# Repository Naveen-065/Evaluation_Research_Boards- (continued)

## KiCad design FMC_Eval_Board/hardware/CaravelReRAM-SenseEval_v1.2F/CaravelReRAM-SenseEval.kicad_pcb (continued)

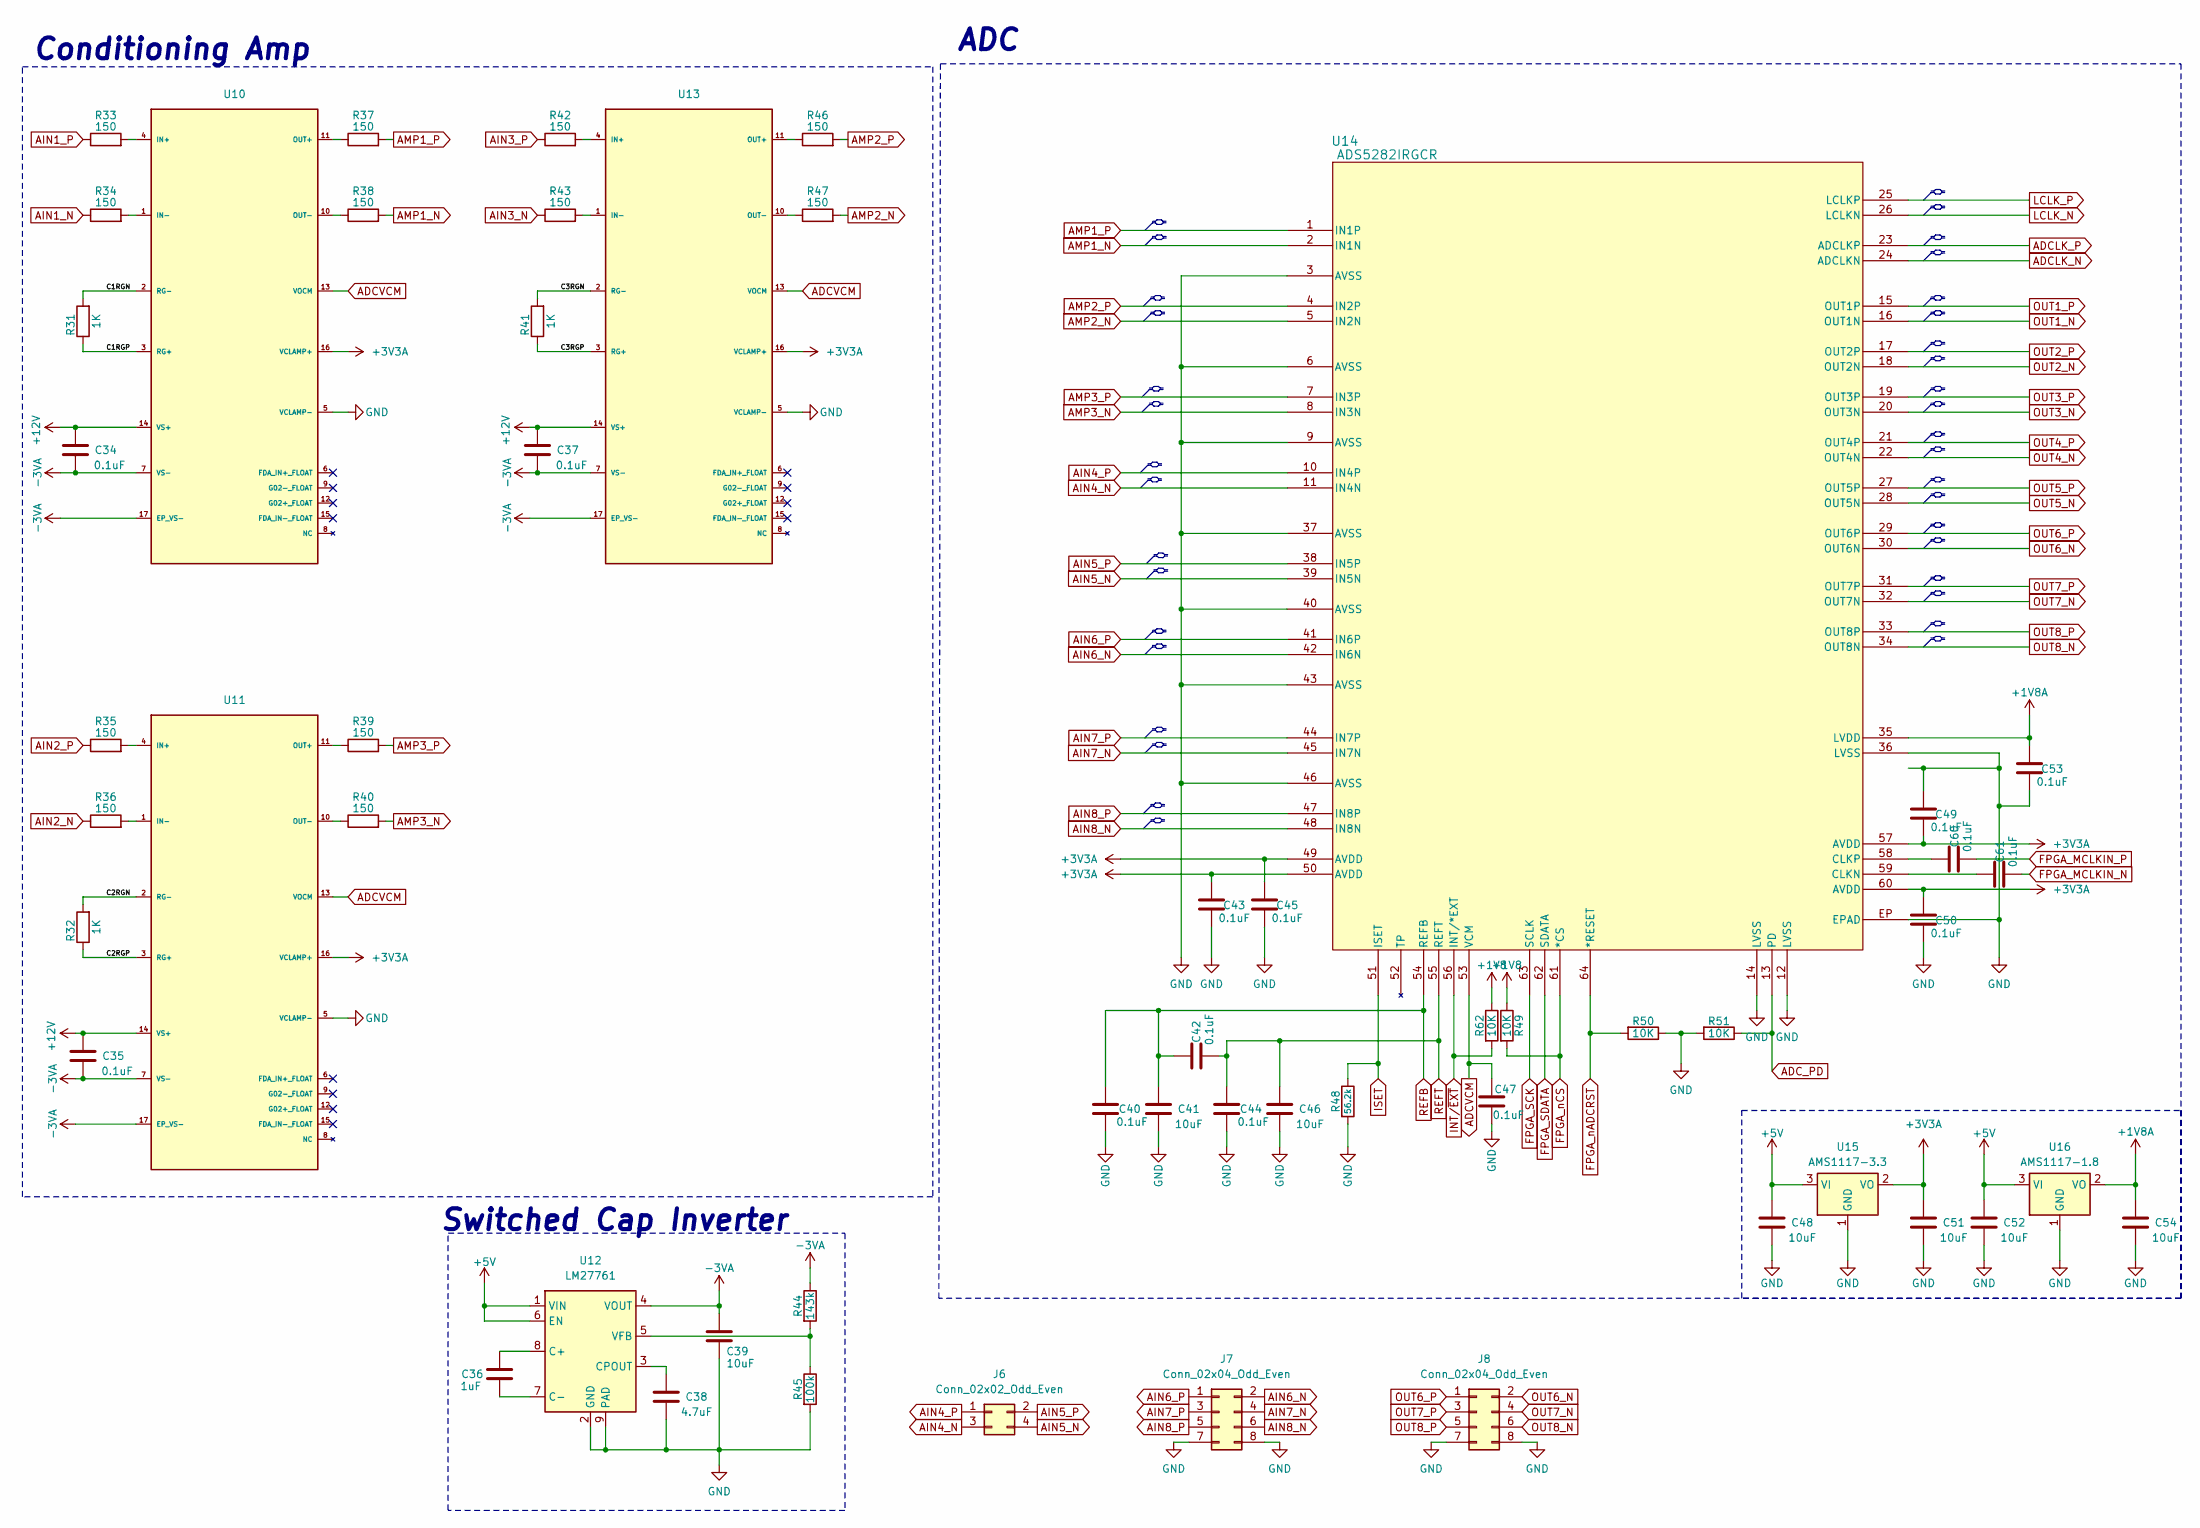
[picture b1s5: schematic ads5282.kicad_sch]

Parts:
C34, C35, C37, C40, C42, C43, C44, C45, C47, C49, C50, C53, C60, C61: 0.1uF; C_0805_2012Metric; Part # C0805C104K5RAC7411
C36: 1uF; C_0805_2012Metric; Part # 885012207103
C38: 4.7uF; C_0805_2012Metric; Part # CL21A475KBQNNNE
C39, C41, C46, C48, C51, C52, C54: 10uF; C_0805_2012Metric; Part # CL21B106KAYQNNE
J6: Conn_02x02_Odd_Even; PinHeader_2x02_P2.00mm_Vertical
J7, J8: Conn_02x04_Odd_Even; IDC-Header_2x04_P2.54mm_Vertical
R31, R32, R41: 1K; R_0805_2012Metric; Part # RC0805FR-071KL
R33, R34, R35, R36, R37, R38, R39, R40, R42, R43, R46, R47: 150; R_0805_2012Metric; Part # RNCP0805FTD150R
R44: 143k; R_0805_2012Metric; Part # RC0805FR-07143KL
R45: 100k; R_0805_2012Metric; Part # RC0805FR-07100KL
R48: 56.2k; R_0805_2012Metric; Part # RC0805FR-1356K2L
R49, R50, R51, R62: 10K; R_0805_2012Metric; Part # RC0805FR-0710KL
U10, U11, U13: INA851RGTR; VQFN16_RGT_TEX; MPN INA851RGTR
U12: LM27761; Texas_DSG0008A_WSON-8-1EP_2x2mm_P0.5mm_EP0.9x1.6mm
U14: ADS5282IRGCR; Texas_RGC0064B_VQFN-64-1EP_9x9mm_P0.5mm_EP4.25x4.25mm
U15: AMS1117-3.3; SOT-223-3_TabPin2
U16: AMS1117-1.8; SOT-223-3_TabPin2

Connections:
+1V8A: C53.2, C54.1, U14.35 (LVDD), U16.2 (VO); also elsewhere on the board
+3V3A: C43.2, C45.2, C49.1, C50.2, C51.1, U10.16 (VCLAMP+), U11.16 (VCLAMP+), U13.16 (VCLAMP+), U14.49 (AVDD), U14.50 (AVDD), U14.57 (AVDD), U14.60 (AVDD), U15.2 (VO)
+5V: C48.1, C52.1, U12.1 (VIN), U12.6 (EN), U15.3 (VI), U16.3 (VI); also elsewhere on the board
+12V: C34.2, C35.2, C37.2, U10.14 (VS+), U11.14 (VS+), U13.14 (VS+); also elsewhere on the board
-3VA: C34.1, C35.1, C37.1, C39.1, R44.1, U10.7 (VS-), U10.17 (EP_VS-), U11.7 (VS-), U11.17 (EP_VS-), U12.4 (VOUT), U13.7 (VS-), U13.17 (EP_VS-)
/ADC/C1RGN: R31.2, U10.2 (RG-)
/ADC/C1RGP: R31.1, U10.3 (RG+)
/ADC/C2RGN: R32.2, U11.2 (RG-)
/ADC/C2RGP: R32.1, U11.3 (RG+)
/ADC/C3RGN: R41.2, U13.2 (RG-)
/ADC/C3RGP: R41.1, U13.3 (RG+)
ADCLK_N: U14.24 (ADCLKN); also elsewhere on the board
ADCLK_P: U14.23 (ADCLKP); also elsewhere on the board
ADCVCM: C47.2, U10.13 (VOCM), U11.13 (VOCM), U13.13 (VOCM), U14.53 (VCM)
ADC_PD: R51.1, U14.13 (PD); also elsewhere on the board
AIN1_N: R34.1; also elsewhere on the board
AIN1_P: R33.1; also elsewhere on the board
AIN2_N: R36.1; also elsewhere on the board
AIN2_P: R35.1; also elsewhere on the board
AIN3_N: R43.1; also elsewhere on the board
AIN3_P: R42.1; also elsewhere on the board
AIN4_N: J6.3, U14.11 (IN4N)
AIN4_P: J6.1, U14.10 (IN4P)
AIN5_N: J6.4, U14.39 (IN5N)
AIN5_P: J6.2, U14.38 (IN5P)
AIN6_N: J7.2, U14.42 (IN6N)
AIN6_P: J7.1, U14.41 (IN6P)
AIN7_N: J7.4, U14.45 (IN7N)
AIN7_P: J7.3, U14.44 (IN7P)
AIN8_N: J7.6, U14.48 (IN8N)
AIN8_P: J7.5, U14.47 (IN8P)
AMP1_N: R38.2, U14.2 (IN1N)
AMP1_P: R37.2, U14.1 (IN1P)
AMP2_N: R47.2, U14.5 (IN2N)
AMP2_P: R46.2, U14.4 (IN2P)
AMP3_N: R40.2, U14.8 (IN3N)
AMP3_P: R39.2, U14.7 (IN3P)
FPGA_SCK: U14.63 (SCLK); also elsewhere on the board
FPGA_SDATA: U14.62 (SDATA); also elsewhere on the board
FPGA_nADCRST: R50.2, U14.64 (*RESET); also elsewhere on the board
FPGA_nCS: R49.2, U14.61 (*CS); also elsewhere on the board
GND: C38.2, C39.2, C40.1, C41.2, C43.1, C44.1, C45.1, C46.2, C47.1, C48.2, C49.2, C50.1, C51.2, C52.2, C53.1, C54.2, J7.7, J7.8, J8.7, J8.8, R45.2, R48.2, R50.1, R51.2, U10.5 (VCLAMP-), U11.5 (VCLAMP-), U12.2 (GND), U12.9 (PAD), U13.5 (VCLAMP-), U14.3 (AVSS), U14.6 (AVSS), U14.9 (AVSS), U14.12 (LVSS), U14.14 (LVSS), U14.36 (LVSS), U14.37 (AVSS), U14.40 (AVSS), U14.43 (LVSS), U14.46 (AVSS), U14.EP (EPAD), U15.1 (GND), U16.1 (GND); also elsewhere on the board
ISET: R48.1, U14.51 (ISET)
LCLK_N: U14.26 (LCLKN); also elsewhere on the board
LCLK_P: U14.25 (LCLKP); also elsewhere on the board
unnamed: R33.2, U10.4 (IN+)
unnamed: R34.2, U10.1 (IN-)
unnamed: R37.1, U10.11 (OUT+)
unnamed: R38.1, U10.10 (OUT-)
unnamed: R35.2, U11.4 (IN+)
unnamed: R36.2, U11.1 (IN-)
unnamed: R39.1, U11.11 (OUT+)
unnamed: R40.1, U11.10 (OUT-)
unnamed: C36.1, U12.8 (C+)
unnamed: C36.2, U12.7 (C-)
unnamed: C38.1, U12.3 (CPOUT)
unnamed: R44.2, R45.1, U12.5 (VFB)
unnamed: R42.2, U13.4 (IN+)
unnamed: R43.2, U13.1 (IN-)
unnamed: R46.1, U13.11 (OUT+)
unnamed: R47.1, U13.10 (OUT-)
OUT1_N: U14.16 (OUT1N); also elsewhere on the board
OUT1_P: U14.15 (OUT1P); also elsewhere on the board
OUT2_N: U14.18 (OUT2N); also elsewhere on the board
OUT2_P: U14.17 (OUT2P); also elsewhere on the board
OUT3_N: U14.20 (OUT3N); also elsewhere on the board
OUT3_P: U14.19 (OUT3P); also elsewhere on the board
OUT4_N: U14.22 (OUT4N); also elsewhere on the board
OUT4_P: U14.21 (OUT4P); also elsewhere on the board
OUT5_N: U14.28 (OUT5N); also elsewhere on the board
OUT5_P: U14.27 (OUT5P); also elsewhere on the board
OUT6_N: J8.2, U14.30 (OUT6P)
OUT6_P: J8.1, U14.29 (OUT6N)
OUT7_N: J8.4, U14.32 (OUT7N)
OUT7_P: J8.3, U14.31 (OUT7P)
OUT8_N: J8.6, U14.34 (OUT8N)
OUT8_P: J8.5, U14.33 (OUT8P)
REFB: C40.2, C41.1, C42.2, U14.54 (REFB)
REFT: C42.1, C44.2, C46.1, U14.55 (REFT)

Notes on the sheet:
Switched Cap Inverter
Conditioning Amp
ADC

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
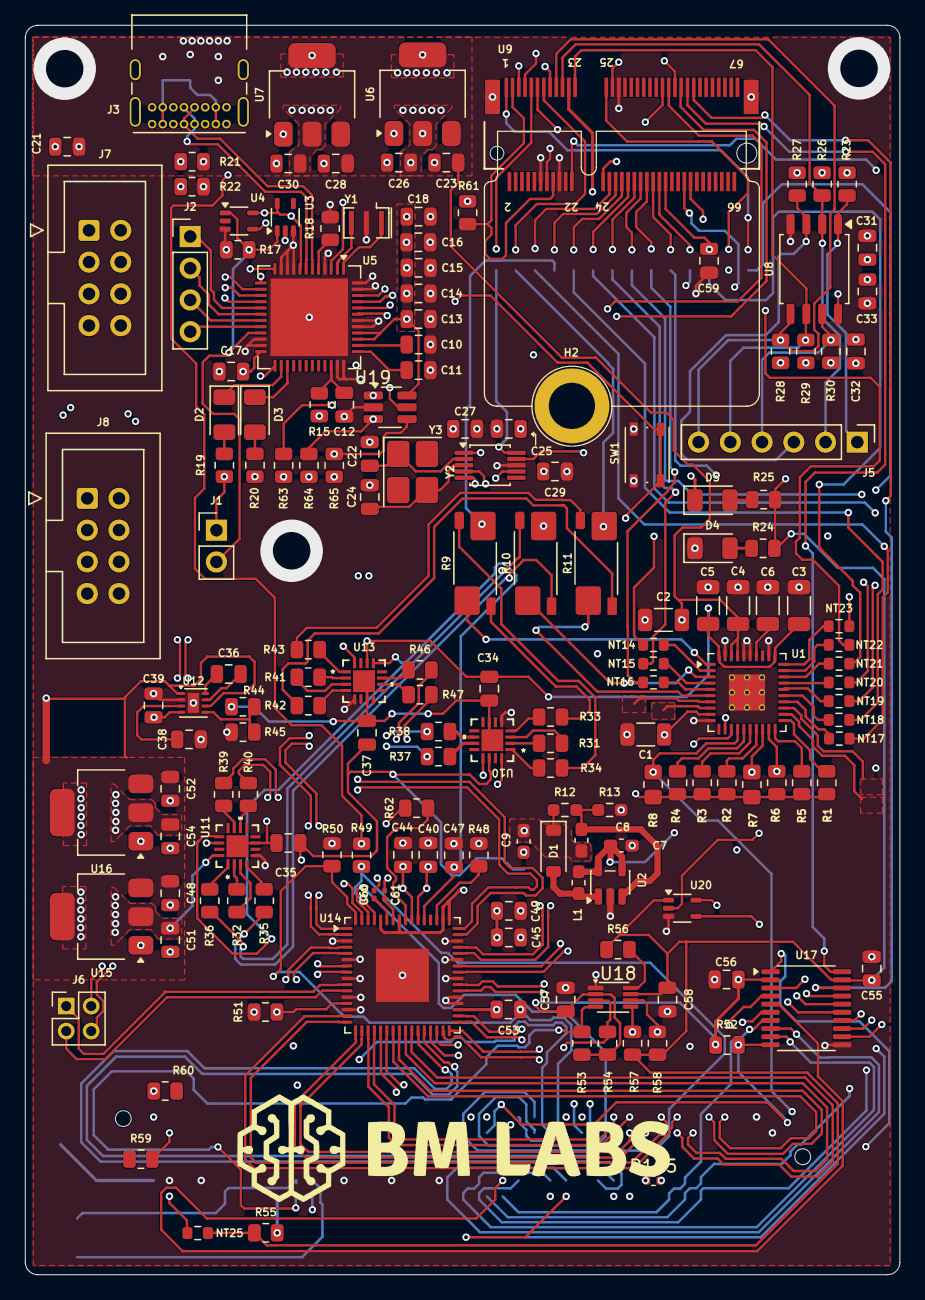
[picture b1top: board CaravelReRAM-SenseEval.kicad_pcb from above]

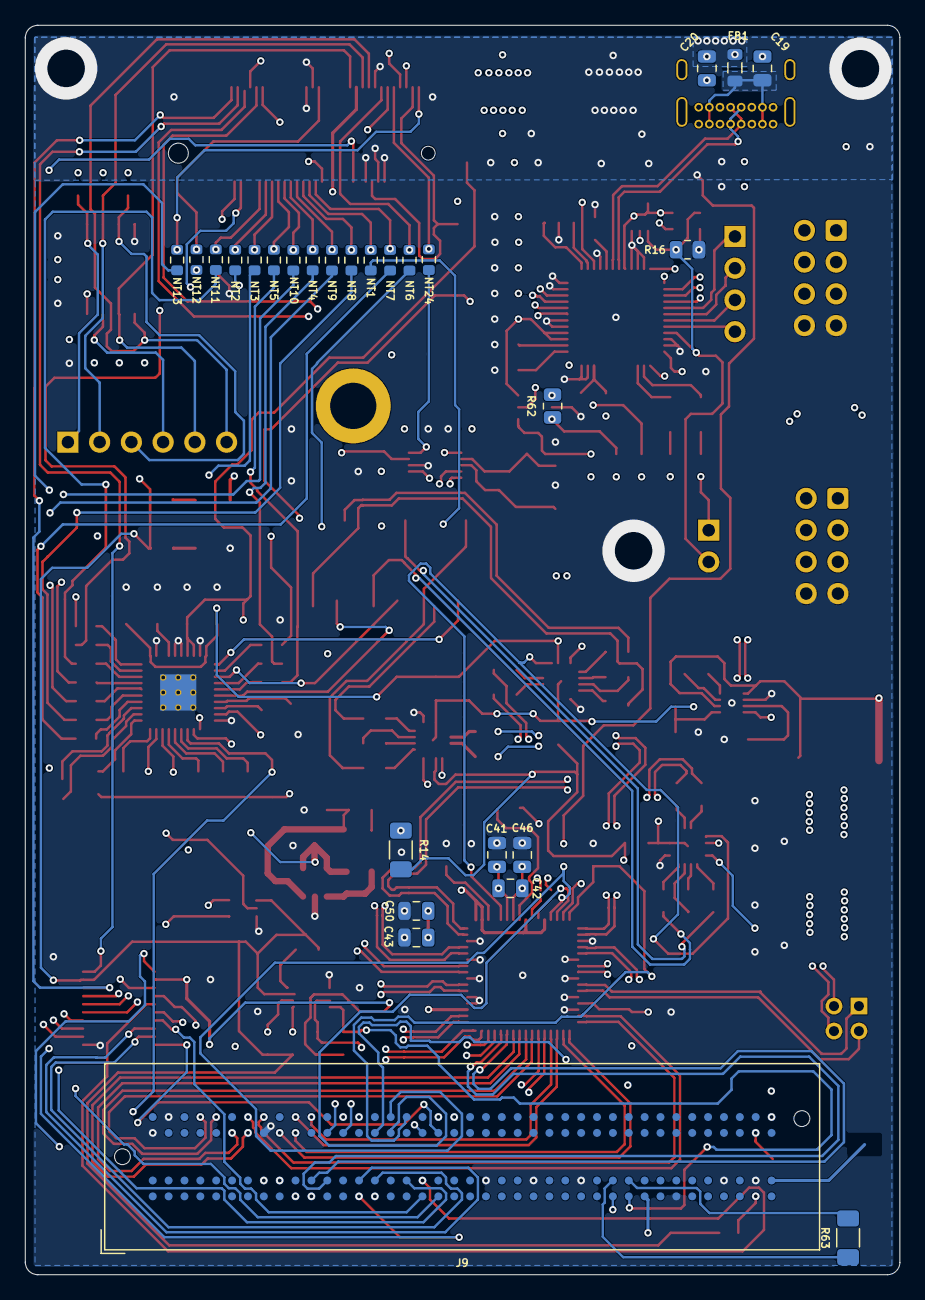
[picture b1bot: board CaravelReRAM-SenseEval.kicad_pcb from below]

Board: 6 copper layers, 70.0 x 100.0 mm, 194 parts (27 on the bottom side), 209 nets.

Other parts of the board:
R62#2: 1K; R_0805_2012Metric
R63#2: ERJ-8GEY0R00V; R_1206_3216Metric_Pad1.30x1.75mm_HandSolder

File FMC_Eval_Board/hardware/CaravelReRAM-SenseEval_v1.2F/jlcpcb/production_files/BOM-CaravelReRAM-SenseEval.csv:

Comment,Designator,Footprint,LCSC,Quantity
0,R61,R_0805_2012Metric,C17477,1
0.01uF,"C12,C19,C31",C_0805_2012Metric,C1710,3
0.1uF,"C10,C11,C13,C14,C15,C16,C17,C20,C27,C29,C32,C34,C35,C37,C40,C42,C43,C44,C45,C47,C49,C50,C53,C55,C56,C57,C58",C_0805_2012Metric,C1711,27
100k,R45,R_0805_2012Metric,C149504,1
100nF,"C1,C2,C3,C4,C5,C6",C_1206_3216Metric,C97946,6
10K,"R15,R21,R22,R23,R26,R27,R28,R29,R30,R49,R50,R51,R52,R53,R54,R55,R56,R57,R58,R59,R60,R64,R65",R_0805_2012Metric,C17414,23
10k,"R1,R2,R3,R4,R5,R6,R7,R8",R_0805_2012Metric,C17414,8
10uF,"C18,C21,C23,C25,C26,C28,C30,C39,C41,C46,C48,C51,C52,C54",C_0805_2012Metric,C15850,14
12K 1%,R18,R_0805_2012Metric,C17444,1
12MHz,Y1,Resonator_SMD_Murata_CSTxExxV-3Pin_3.0x1.1mm,C341520,1
143k,R44,R_0805_2012Metric,C2930167,1
150,"R19,R20,R33,R34,R35,R36,R37,R38,R39,R40,R42,R43,R46,R47",R_0805_2012Metric,C17471,14
18pF,"C22,C24",C_0805_2012Metric,C527079,2
1K,"R16,R17,R24,R25,R31,R32,R41,R62",R_0805_2012Metric,C2907232,8
1uF,"C33,C36,C59",C_0805_2012Metric,C28323,3
4.7uF,C38,C_0805_2012Metric,C1779,1
434133025816,SW1,SW_Push_1P1T_NO_Vertical_Wuerth_434133025816,C5504987,1
470R,"R10,R11,R9",R_Shunt_Vishay_WSK2512_6332Metric_T1.19mm,C7420029,3
56.2k,R48,R_0805_2012Metric,C2933471,1
600R/0.5A,FB1,L_0805_2012Metric,C5523406,1
93LCxxBxxOT,U19,SOT-23-6_Handsoldering,C190271,1
ADS5282IRGCR,U14,Texas_RGC0064B_VQFN-64-1EP_9x9mm_P0.5mm_EP4.25x4.25mm,C2670909,1
AMS1117-1.8,"U16,U7",SOT-223-3_TabPin2,C7380514,2
AMS1117-3.3,"U15,U6",SOT-223-3_TabPin2,C6186,2
ASP-134604-01,J9,Samtec_FMC_ASP-134604-01_4x40_Vertical,C2830435,1
CL10C4R7BB8NNNC,C8,C_0603_1608Metric_Pad1.08x0.95mm_HandSolder,C307509,1
C_0201_0603Metric,"C60,C61",C_0201_0603Metric,C49062,2
Conn_01x02_Pin,J1,PinHeader_1x02_P2.54mm_Vertical,C32713268,1
Conn_01x04_Pin,J2,PinHeader_1x04_P2.54mm_Vertical,C52016392,1
Conn_01x06_Pin,J5,PinHeader_1x06_P2.54mm_Vertical,C32713272,1
Conn_02x02_Odd_Even,J6,PinHeader_2x02_P2.00mm_Vertical,C5383103,1
Conn_02x04_Odd_Even,"J7,J8",IDC-Header_2x04_P2.54mm_Vertical,C9135,2
DAC81416RHAT,U1,Texas_RHA0040D_VQFN-40-1EP_6x6mm_P0.5mm_EP2.9x2.9mm_ThermalVias,C2680104,1
ERA-3AEB2053V,R13,R_0603_1608Metric_Pad0.98x0.95mm_HandSolder,C22949,1
ERJ-8GEY0R00V,"R14,R63",R_1206_3216Metric_Pad1.30x1.75mm_HandSolder,C2907406,2
FA-238 25.0000MB-C3,Y2,Crystal_SMD_3225-4Pin_3.2x2.5mm_HandSoldering,C70593,1
FT232H,U5,QFN-48-1EP_8x8mm_P0.5mm_EP6.2x6.2mm,C82158,1
GRM188R61E475KE11D,"C7,C9",C_0603_1608Metric_Pad1.08x0.95mm_HandSolder,C90057,2
INA851RGTR,"U10,U11,U13",VQFN16_RGT_TEX,C5371575,3
LM27761,U12,Texas_DSG0008A_WSON-8-1EP_2x2mm_P0.5mm_EP0.9x1.6mm,C129351,1
M.2-CONNECTOR-E,U9,M.2-CONNECTOR-E,C2977809,1
MBR0530,D1,D_SOD-123,C82046,1
MCT06030C1804FP500,R12,R_0603_1608Metric_Pad0.98x0.95mm_HandSolder,C13318,1
MLZ1608N100LT000,L1,L_0603_1608Metric_Pad1.05x0.95mm_HandSolder,C194437,1
NetTie_2,"NT1,NT10,NT11,NT12,NT13,NT14,NT15,NT16,NT17,NT18,NT19,NT2,NT20,NT21,NT23,NT24,NT3,NT4,NT5,NT6,NT7,NT8,NT9",R_0603_1608Metric,C21189,23
RED,"D2,D3,D4,D5",LED_1206_3216Metric,C84270,4
R_0402_1005Metric,R165,R_0402_1005Metric,C25076,1
SN74LVC1G125DCKR,"U3,U4",Texas_R-PDSO-G5_DCK-5,C7833,2
Si5351A-B-GT,Y3,MSOP-10_3x3mm_P0.5mm,C504891,1
TPS61040DDC,U2,SOT-23-5,C2678707,1
TXS0108EPW,U17,TSSOP-20_4.4x6.5mm_P0.65mm,C17206,1
USB_C_Receptacle_USB2.0_16P,J3,USB_C_Receptacle_GCT_USB4085,C7095263,1
VSSOP-8_2.3x2mm_P0.5mm,U18,VSSOP-8_2.3x2mm_P0.5mm,C33196,1
W25Q32FVSS,U8,SOIC-8_5.3x5.3mm_P1.27mm,C29067,1
MICROMOD-Standoff,H2,MicroMod-Standoff,,1

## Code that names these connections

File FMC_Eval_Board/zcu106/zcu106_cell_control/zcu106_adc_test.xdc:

# ZCU106 300 MHz USER_SI570 clock and PL user LED.
set_property PACKAGE_PIN AH12 [get_ports sysclk_p]
set_property PACKAGE_PIN AJ12 [get_ports sysclk_n]
set_property IOSTANDARD DIFF_SSTL12 [get_ports {sysclk_p sysclk_n}]
create_clock -name sysclk_300mhz -period 3.333 [get_ports sysclk_p]

set_property PACKAGE_PIN AL11 [get_ports led0]
set_property IOSTANDARD LVCMOS12 [get_ports led0]
set_property DRIVE 4 [get_ports led0]
set_property SLEW SLOW [get_ports led0]

# FMC HPC0/J5.  Every used connector signal belongs to the LPC subset.
# The shared VADJ_FMC rail must be 1.8 V before this image is programmed.
set_property PACKAGE_PIN H19 [get_ports out4_p]
set_property PACKAGE_PIN G19 [get_ports out4_n]
set_property PACKAGE_PIN K17 [get_ports out5_p]
set_property PACKAGE_PIN J17 [get_ports out5_n]
set_property PACKAGE_PIN F17 [get_ports lclk_p]
set_property PACKAGE_PIN F16 [get_ports lclk_n]
set_property PACKAGE_PIN K19 [get_ports out2_p]
set_property PACKAGE_PIN K18 [get_ports out2_n]
set_property PACKAGE_PIN E15 [get_ports adclk_p]
set_property PACKAGE_PIN E14 [get_ports adclk_n]
set_property PACKAGE_PIN L20 [get_ports out1_p]
set_property PACKAGE_PIN K20 [get_ports out1_n]
set_property PACKAGE_PIN L17 [get_ports out3_p]
set_property PACKAGE_PIN L16 [get_ports out3_n]
set_property IOSTANDARD LVDS [get_ports {
    out4_p out4_n out5_p out5_n lclk_p lclk_n out2_p out2_n
    adclk_p adclk_n out1_p out1_n out3_p out3_n
}]
set_property DIFF_TERM_ADV TERM_NONE [get_ports {
    out4_p out4_n out5_p out5_n lclk_p lclk_n out2_p out2_n
    adclk_p adclk_n out1_p out1_n out3_p out3_n
}]
create_clock -name adc_lclk -period 16.667 [get_ports lclk_p]
set_clock_groups -asynchronous \
    -group [get_clocks -include_generated_clocks sysclk_300mhz] \
    -group [get_clocks adc_lclk]

# LA01, connector D8/D9.  D9 is intentionally a driven-low reference.
set_property PACKAGE_PIN H18 [get_ports fpga_mclkin_p]
set_property PACKAGE_PIN H17 [get_ports fpga_mclkin_n]
set_property IOSTANDARD LVCMOS18 [get_ports {fpga_mclkin_p fpga_mclkin_n}]
set_property DRIVE 12 [get_ports {fpga_mclkin_p fpga_mclkin_n}]
set_property SLEW SLOW [get_ports {fpga_mclkin_p fpga_mclkin_n}]

# Other mezzanine-to-FPGA signals.
set_property PACKAGE_PIN L15 [get_ports fpga_rx]
set_property PACKAGE_PIN C13 [get_ports scan_si]
set_property PACKAGE_PIN H16 [get_ports ready_i]
set_property PACKAGE_PIN G16 [get_ports reset_b]
set_property PACKAGE_PIN D16 [get_ports si5351_clk1_1v8]
set_property IOSTANDARD LVCMOS18 [get_ports {
    fpga_rx scan_si ready_i reset_b si5351_clk1_1v8
}]
set_property PULLTYPE NONE [get_ports {
    fpga_rx scan_si ready_i reset_b si5351_clk1_1v8
}]

# FPGA-to-mezzanine control signals.
set_property PACKAGE_PIN K15 [get_ports fpga_tx]
set_property PACKAGE_PIN C12 [get_ports scan_cc]
set_property PACKAGE_PIN G15 [get_ports scan_se]
set_property PACKAGE_PIN F15 [get_ports scan_tm]
set_property PACKAGE_PIN E18 [get_ports aq1_sck]
set_property PACKAGE_PIN E17 [get_ports aq1_mosi]
set_property PACKAGE_PIN G18 [get_ports fpga_sck]
set_property PACKAGE_PIN F18 [get_ports fpga_sdata]
set_property PACKAGE_PIN D17 [get_ports adc_pd]
set_property PACKAGE_PIN C17 [get_ports fpga_loe]
set_property PACKAGE_PIN J16 [get_ports aq1_ncs]
set_property PACKAGE_PIN J15 [get_ports aq1_nldac]
set_property PACKAGE_PIN A13 [get_ports fpga_ncs]
set_property PACKAGE_PIN A12 [get_ports fpga_nadcrst]
set_property PACKAGE_PIN C16 [get_ports aq1_nrst]
set_property IOSTANDARD LVCMOS18 [get_ports {
    fpga_tx scan_cc scan_se scan_tm aq1_sck aq1_mosi fpga_sck
    fpga_sdata adc_pd fpga_loe aq1_ncs aq1_nldac fpga_ncs
    fpga_nadcrst aq1_nrst
}]
set_property DRIVE 4 [get_ports {
    fpga_tx scan_cc scan_se scan_tm aq1_sck aq1_mosi fpga_sck
    fpga_sdata adc_pd fpga_loe aq1_ncs aq1_nldac fpga_ncs
    fpga_nadcrst aq1_nrst scan_si reset_b
}]
set_property SLEW SLOW [get_ports {
    fpga_tx scan_cc scan_se scan_tm aq1_sck aq1_mosi fpga_sck
    fpga_sdata adc_pd fpga_loe aq1_ncs aq1_nldac fpga_ncs
    fpga_nadcrst aq1_nrst scan_si reset_b
}]
set_property PULLTYPE NONE [get_ports {
    fpga_tx scan_cc scan_se scan_tm aq1_sck aq1_mosi fpga_sck
    fpga_sdata adc_pd fpga_loe aq1_ncs aq1_nldac fpga_ncs
    fpga_nadcrst aq1_nrst
}]

set_false_path -to [get_cells -hier -filter {NAME =~ *input_sync_1_reg*}]
set_false_path -to [get_cells -hier -filter {NAME =~ scan_reader/*_sync_reg[0]}]
set_property BITSTREAM.CONFIG.UNUSEDPIN Pullnone [current_design]
